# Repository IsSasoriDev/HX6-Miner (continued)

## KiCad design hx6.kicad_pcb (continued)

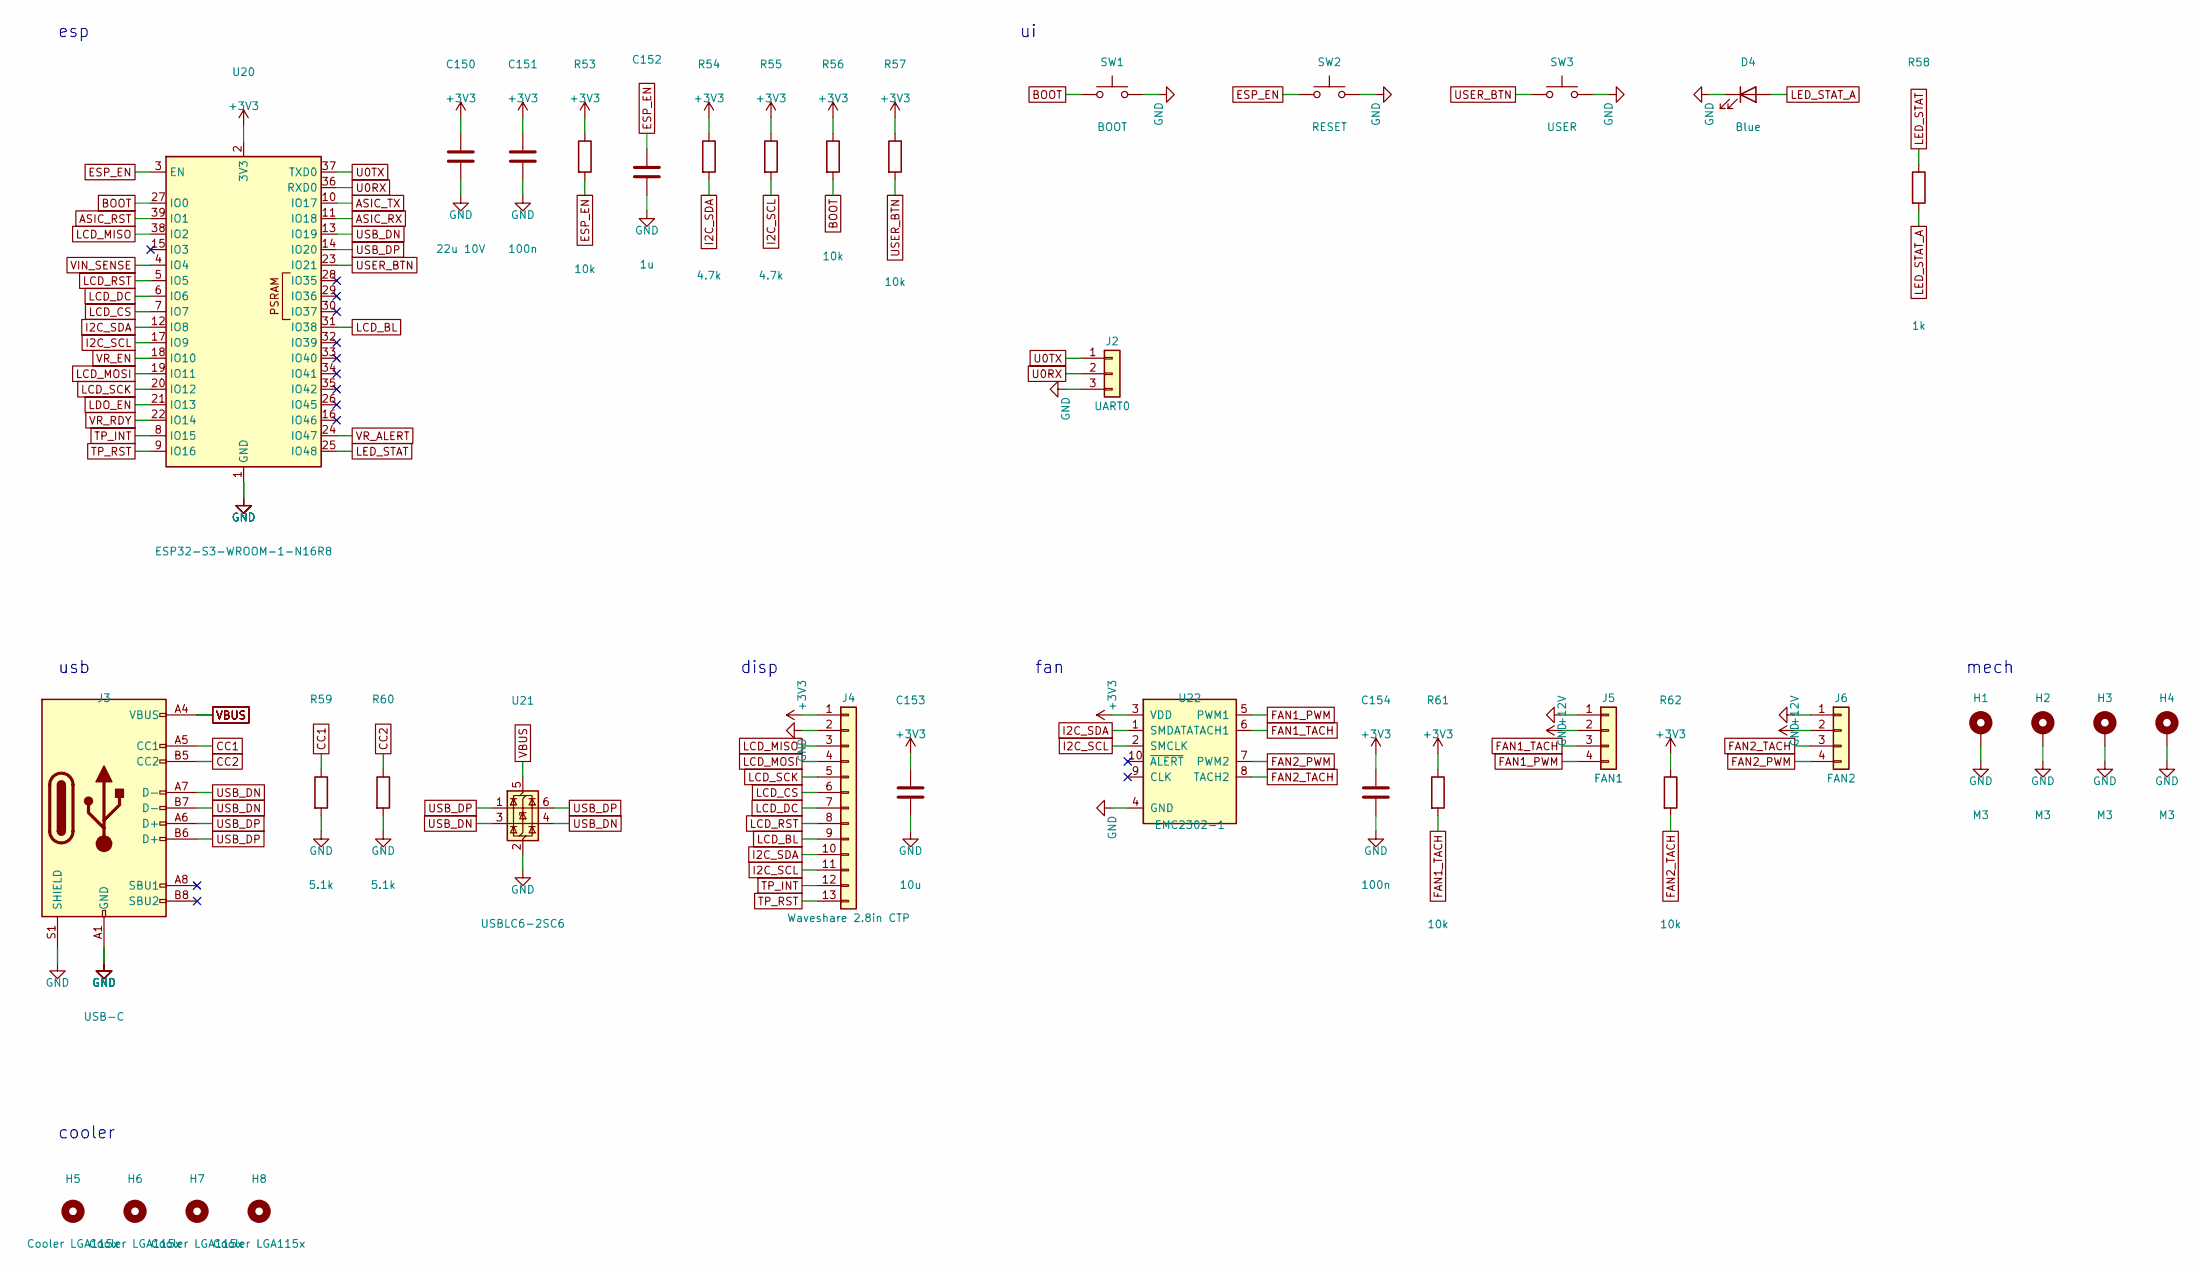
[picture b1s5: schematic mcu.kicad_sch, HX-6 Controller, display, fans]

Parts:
C150: 22u 10V; C_0805_2012Metric
C151, C154: 100n; C_0402_1005Metric
C152: 1u; C_0603_1608Metric
C153: 10u; C_0805_2012Metric
D4: Blue; LED_0603_1608Metric
H1, H2, H3, H4: M3; MountingHole_3.2mm_M3_Pad_Via
H5, H6, H7, H8: Cooler LGA115x; CoolerHole_4.0mm_NPTH
J2: UART0; PinHeader_1x03_P2.54mm_Vertical
J3: USB-C; USB_C_Receptacle_HRO_TYPE-C-31-M-12; MPN HRO TYPE-C-31-M-12
J4: Waveshare 2.8in CTP; JST_GH_SM13B-GHS-TB_1x13-1MP_P1.25mm_Horizontal; MPN JST SM13B-GHS-TB (GH 1.25 mm, 13 pin)
J5: FAN1; FanPinHeader_1x04_P2.54mm_Vertical; MPN Molex 47053-1000
J6: FAN2; FanPinHeader_1x04_P2.54mm_Vertical; MPN Molex 47053-1000
R53, R56, R57, R61, R62: 10k; R_0402_1005Metric
R54, R55: 4.7k; R_0402_1005Metric
R58: 1k; R_0402_1005Metric
R59, R60: 5.1k; R_0402_1005Metric
SW1: BOOT; SW_SPST_TL3342; MPN TE FSMSM / TL3342
SW2: RESET; SW_SPST_TL3342; MPN TE FSMSM / TL3342
SW3: USER; SW_SPST_TL3342; MPN TE FSMSM / TL3342
U20: ESP32-S3-WROOM-1-N16R8; ESP32-S3-WROOM-1; MPN ESP32-S3-WROOM-1-N16R8
U21: USBLC6-2SC6; SOT-23-6; MPN USBLC6-2SC6
U22: EMC2302-1; MSOP-10_3x3mm_P0.5mm; MPN EMC2302-1-AIZL

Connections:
+3V3: C150.1, C151.1, C153.1, C154.1, J4.1, R53.1, R54.1, R55.1, R56.1, R57.1, R61.1, R62.1, U20.2 (3V3), U22.3 (VDD); also elsewhere on the board
+12V: J5.2, J6.2; also elsewhere on the board
ASIC_RST: U20.39 (IO1); also elsewhere on the board
ASIC_RX: U20.11 (IO18); also elsewhere on the board
ASIC_TX: U20.10 (IO17); also elsewhere on the board
BOOT: R56.2, SW1.1, U20.27 (IO0)
CC1: J3.A5 (CC1), R59.1
CC2: J3.B5 (CC2), R60.1
ESP_EN: C152.1, R53.2, SW2.1, U20.3 (EN)
FAN1_PWM: J5.4, U22.5 (PWM1)
FAN1_TACH: J5.3, R61.2, U22.6 (TACH1)
FAN2_PWM: J6.4, U22.7 (PWM2)
FAN2_TACH: J6.3, R62.2, U22.8 (TACH2)
GND: C150.2, C151.2, C152.2, C153.2, C154.2, D4.1 (K), H1.1, H2.1, H3.1, H4.1, J2.3, J3.A1 (GND), J3.A12 (GND), J3.B1 (GND), J3.B12 (GND), J3.S1 (SHIELD), J4.2, J5.1, J6.1, R59.2, R60.2, SW1.2, SW2.2, SW3.2, U20.1 (GND), U20.40 (GND), U20.41 (GND), U21.2 (GND), U22.4 (GND); also elsewhere on the board
I2C_SCL: J4.11, R55.2, U20.17 (IO9), U22.2 (SMCLK); also elsewhere on the board
I2C_SDA: J4.10, R54.2, U20.12 (IO8), U22.1 (SMDATA); also elsewhere on the board
LCD_BL: J4.9, U20.31 (IO38)
LCD_CS: J4.6, U20.7 (IO7)
LCD_DC: J4.7, U20.6 (IO6)
LCD_MISO: J4.3, U20.38 (IO2)
LCD_MOSI: J4.4, U20.19 (IO11)
LCD_RST: J4.8, U20.5 (IO5)
LCD_SCK: J4.5, U20.20 (IO12)
LDO_EN: U20.21 (IO13); also elsewhere on the board
LED_STAT: R58.1, U20.25 (IO48)
LED_STAT_A: D4.2 (A), R58.2
TP_INT: J4.12, U20.8 (IO15)
TP_RST: J4.13, U20.9 (IO16)
U0RX: J2.2, U20.36 (RXD0)
U0TX: J2.1, U20.37 (TXD0)
USB_DN: J3.A7 (D-), J3.B7 (D-), U20.13 (IO19), U21.3 (I/O2), U21.4 (I/O2)
USB_DP: J3.A6 (D+), J3.B6 (D+), U20.14 (IO20), U21.1 (I/O1), U21.6 (I/O1)
USER_BTN: R57.2, SW3.1, U20.23 (IO21)
VBUS: J3.A4 (VBUS), J3.A9 (VBUS), J3.B4 (VBUS), J3.B9 (VBUS), U21.5 (VBUS); also elsewhere on the board
VIN_SENSE: U20.4 (IO4); also elsewhere on the board
VR_ALERT: U20.24 (IO47); also elsewhere on the board
VR_EN: U20.18 (IO10); also elsewhere on the board
VR_RDY: U20.22 (IO14); also elsewhere on the board

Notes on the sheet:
esp
usb
disp
fan
mech
cooler

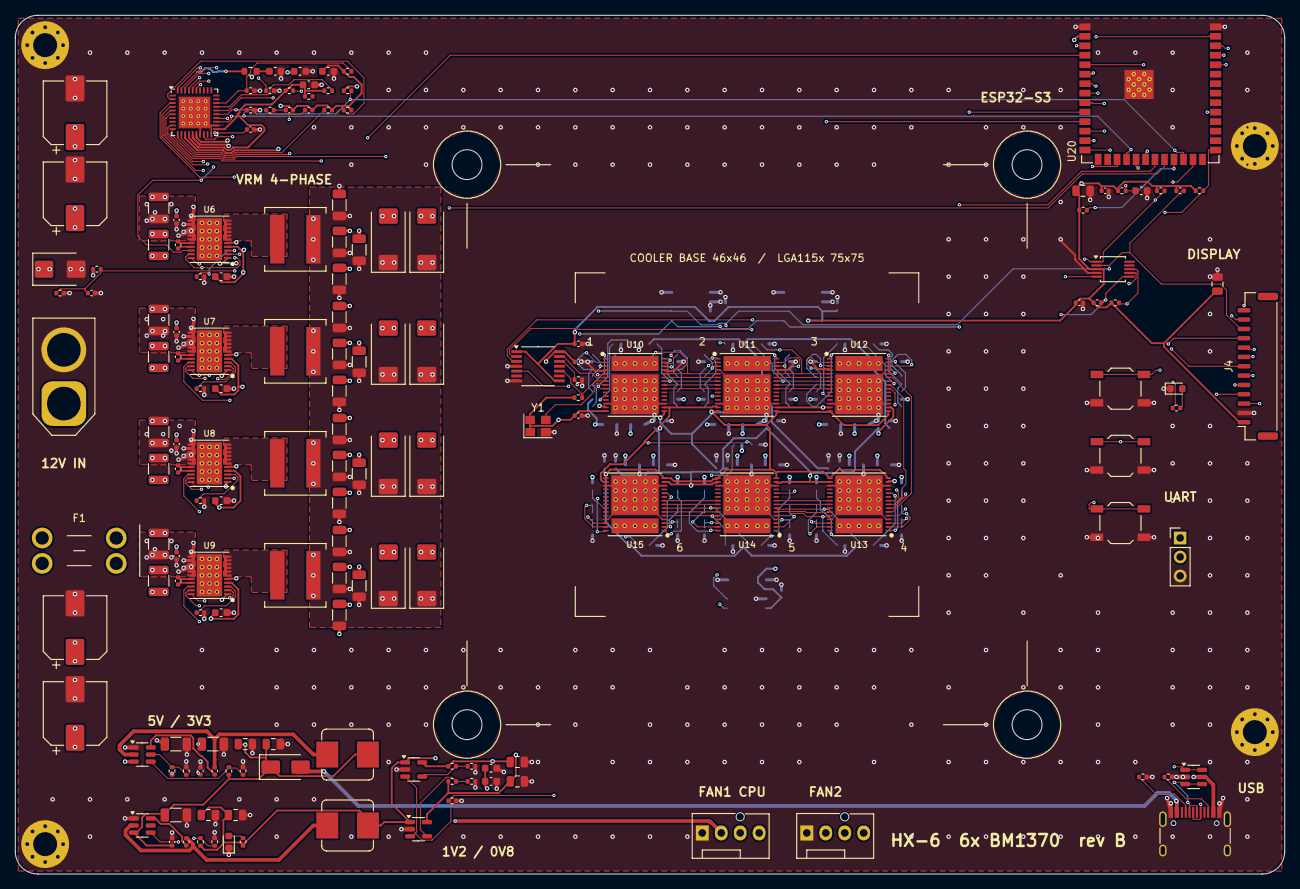
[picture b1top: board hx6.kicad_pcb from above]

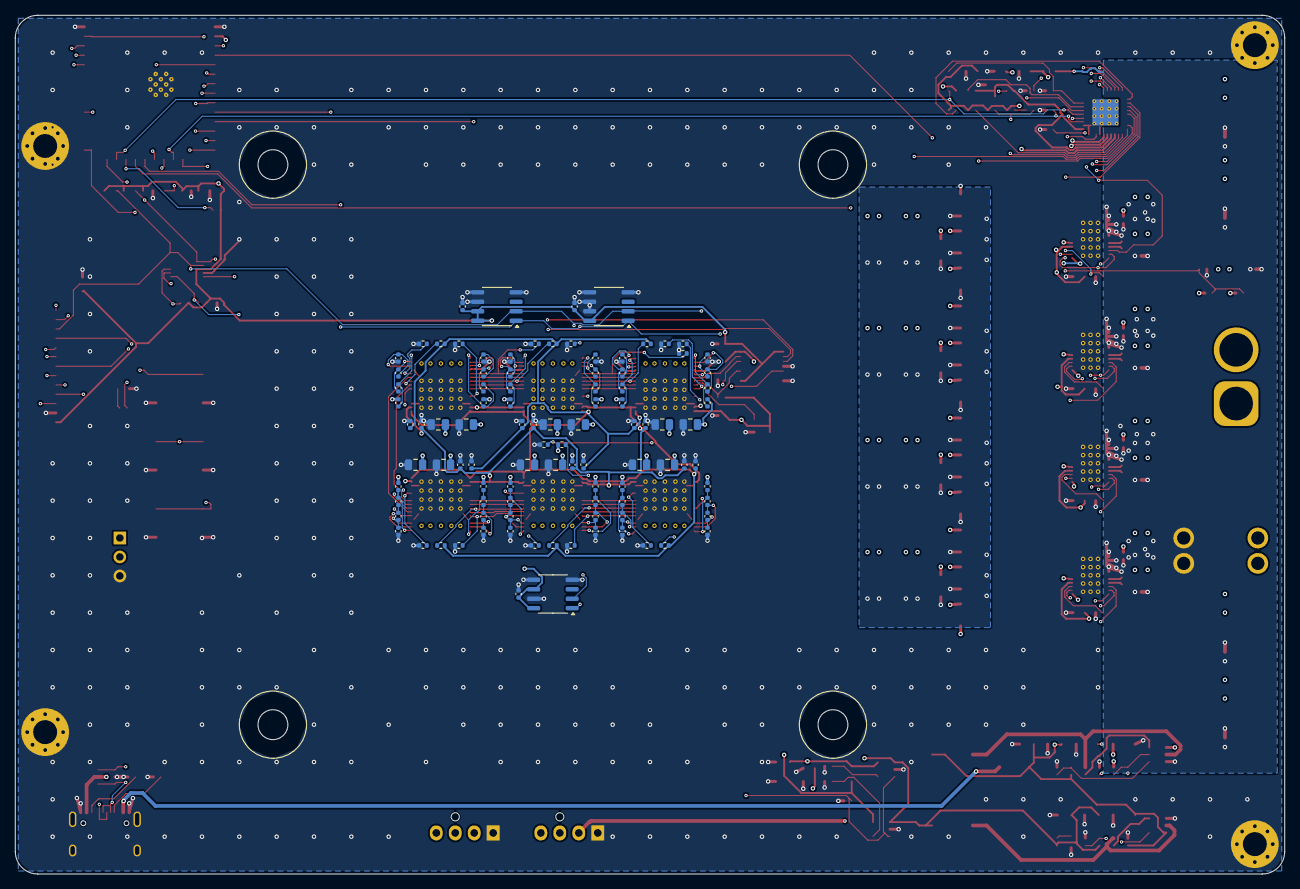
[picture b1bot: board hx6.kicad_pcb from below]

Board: 6 copper layers, 170.0 x 115.0 mm, 267 parts (98 on the bottom side), 163 nets.

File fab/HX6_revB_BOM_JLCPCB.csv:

Comment,Designator,Footprint,Quantity,Manufacturer Part,LCSC Part #
XT60 12V in,J1,AMASS_XT60-M_1x02_P7.20mm_Vertical,1,AMASS XT60PW-M (vertical),
15A mini blade,F1,Fuseholder_Blade_Mini_Keystone_3568,1,Keystone 3568 holder + 15 A mini blade fuse,
SMBJ15CA,D1,D_SMB,1,SMBJ15CA (bidirectional),
270u 16V,"C1,C2,C3,C4",CP_Elec_8x10,4,Panasonic 16SVPF270M (polymer),
100k,"R1,R3,R5,R7,R14,R23",R_0402_1005Metric,6,,
10k,"R2,R11,R13,R16,R19,R21,R22,R24,R34,R35,R36,R38,R39,R41,R42,R44,R45,R47,R48,R50,R51,R52,R53,R56,R57,R61,R62",R_0402_1005Metric,27,,
100n,"C5,C8,C9,C13,C14,C80,C81,C92,C93,C104,C105,C116,C117,C128,C129,C140,C141,C144,C145,C146,C147,C148,C149,C151,C154",C_0402_1005Metric,25,,
TPS54302,"U1,U2",SOT-23-6,2,TPS54302DDCR,
33k,R4,R_0402_1005Metric,1,,
10u 25V,"C6,C7,C12",C_1206_3216Metric,3,,
10u,L1,L_Bourns_SRP7028A_7.3x6.6mm,1,Bourns SRP7028A-100M,
13.3k,R6,R_0402_1005Metric,1,,
22u 10V,"C10,C11,C15,C16,C150",C_0805_2012Metric,5,,
SS34,D2,D_SMA,1,SS34,
6.8u,L2,L_Bourns_SRP7028A_7.3x6.6mm,1,Bourns SRP7028A-6R8M,
22.1k,R8,R_0402_1005Metric,1,,
Green,D3,LED_0603_1608Metric,1,,
1k,"R9,R33,R37,R40,R43,R46,R49,R58",R_0402_1005Metric,8,,
TLV75801,"U3,U4",SOT-23-5,2,TLV75801PDBVR,
12k,R10,R_0402_1005Metric,1,,
1u,"C17,C19,C22,C24,C29,C40,C51,C62,C152",C_0603_1608Metric,9,,
10u,"C18,C20,C153",C_0805_2012Metric,3,,
4.53k,R12,R_0402_1005Metric,1,,
TPS53647,U5,Texas_RHA0040B_VQFN-40-1EP_6x6mm_P0.5mm_EP4.15x4.15mm_ThermalVias,1,TPS53647RTAR,
10,R15,R_0603_1608Metric,1,,
1u 25V,C21,C_0603_1608Metric,1,,
2.2u,C23,C_0603_1608Metric,1,,
14.7k,R17,R_0402_1005Metric,1,,
150k,R18,R_0402_1005Metric,1,,
2.2n,C25,C_0402_1005Metric,1,,
47p,C26,C_0402_1005Metric,1,,
0,"R25,R27,R28",R_0402_1005Metric,3,,
75k,R26,R_0402_1005Metric,1,,
1n,C27,C_0402_1005Metric,1,,
CSD95490Q5MC,"U6,U7,U8,U9",TI_DMC0012A_VSON-CLIP_5x6mm,4,CSD95490Q5MC,
110k,"R29,R30,R31,R32",R_0402_1005Metric,4,,
100n 16V,"C28,C39,C50,C61",C_0402_1005Metric,4,,
22u 25V,"C30,C31,C41,C42,C52,C53,C63,C64",C_1210_3225Metric,8,,
100n 25V,"C32,C43,C54,C65",C_0402_1005Metric,4,,
150n,"L3,L4,L5,L6",L_Coilcraft_XAL7070-XXX,4,Coilcraft XAL7070-151MEC,
47u 6.3V,"C33,C34,C35,C36,C44,C45,C46,C47,C55,C56,C57,C58,C66,C67,C68,C69",C_1206_3216Metric,16,,
470u 2.5V,"C37,C38,C48,C49,C59,C60,C70,C71",CP_EIA-7343-31_Kemet-D,8,Panasonic 2R5TPF470M6L (POSCAP),
BM1370,"U10,U11,U12,U13,U14,U15",BM1370,6,Bitmain BM1370,
1u 25V,"C72,C73,C74,C75,C76,C77,C78,C79,C84,C85,C86,C87,C88,C89,C90,C91,C96,C97,C98,C99,C100,C101,C102,C103,C108,C109,C110,C111,C112,C113,C114,C115,C120,C121,C122,C123,C124,C125,C126,C127,C132,C133,C134,C135,C136,C137,C138,C139",C_0402_1005Metric,48,,
22u 6.3V,"C82,C83,C94,C95,C106,C107,C118,C119,C130,C131,C142,C143",C_0805_2012Metric,12,,
TXU0304,U16,TSSOP-14_4.4x5mm_P0.65mm,1,TXU0304PWR,
25MHz 1.2V,Y1,Oscillator_SMD_Abracon_ASE-4Pin_3.2x2.5mm,1,Taitien OXLTDLJANF-25.000000 (1.2 V CMOS),
TMP1075,"U17,U18,U19",SO-8_3.9x4.9mm_P1.27mm,3,TMP1075DR,
ESP32-S3-WROOM-1-N16R8,U20,ESP32-S3-WROOM-1,1,ESP32-S3-WROOM-1-N16R8,
4.7k,"R54,R55",R_0402_1005Metric,2,,
BOOT,SW1,SW_SPST_TL3342,1,TE FSMSM / TL3342,
RESET,SW2,SW_SPST_TL3342,1,TE FSMSM / TL3342,
USER,SW3,SW_SPST_TL3342,1,TE FSMSM / TL3342,
Blue,D4,LED_0603_1608Metric,1,,
UART0,J2,PinHeader_1x03_P2.54mm_Vertical,1,,
USB-C,J3,USB_C_Receptacle_HRO_TYPE-C-31-M-12,1,HRO TYPE-C-31-M-12,
5.1k,"R59,R60",R_0402_1005Metric,2,,
USBLC6-2SC6,U21,SOT-23-6,1,USBLC6-2SC6,
Waveshare 2.8in CTP,J4,JST_GH_SM13B-GHS-TB_1x13-1MP_P1.25mm_Horizontal,1,"JST SM13B-GHS-TB (GH 1.25 mm, 13 pin)",
EMC2302-1,U22,MSOP-10_3x3mm_P0.5mm,1,EMC2302-1-AIZL,
FAN1,J5,FanPinHeader_1x04_P2.54mm_Vertical,1,Molex 47053-1000,
FAN2,J6,FanPinHeader_1x04_P2.54mm_Vertical,1,Molex 47053-1000,
